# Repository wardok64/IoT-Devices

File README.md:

# Basic IoT devices to measure different field variables (based on Zigbee and MQTT)

This document details the final and functional design of a network of wireless sensors, established as End Devices and Coordinator within a Zigbee network, which, through its gateway consisting of the coordinator and an ESP12 communicated via UART data is sent to a MQTT Broker, and from there, it is possible to digitally display the data through NodeRED Dashboard.

The data sent from the end devices pertains to the value of the associated field sensor (it can be temperature, humidity or current), as well as the charge value of the battery that is powering it, in order to monitor the battery life and to protect the end device from low voltage.

## Initial requirements:

- Scalable software level via Zigbee and Node-RED.
- Battery powered field devices.
- Use MCU or development board with minimal elements to maximise power savings.
- Develop firmware with power saving option: "LowPower.h"/"RTCZero.h".
- Standard power supply for all field devices (3.3VDC).
- Scalability at hardware level.
- In the case of sensors with analogue signal, consider an ADC resolution between 12 and 16-bits.
- Low voltage protection in main power supply. (consider alarm via Zigbee).

## Sketch idea:

## Core materials HW:

- Seeeduino XIAO (ARM Cortex-M0+ CPU(SAMD21G18) running at up to 48MHz)
- Xbee XBP24 module Digi (XbeePROS2B).
- ESP8266/ESP-12 package.
- Raspberry Pi Zero W.

## Core Arduino libraries:

- Xbee.h
- PubSubClient.h
- RTCZero.h

## Software requirements:
  
- ArduinoIDE/VSC.
- XCTU (Digi).
- Node-RED/Dashboard.
- Mosquitto Broker.
- KiCAD.

## Sensors:

### Current:
- SCT-019-000 Current sensor/ Input current: 0-200A/ Output: 0-33mA (It needs burden resistor to convert to voltage).
- SCT-013-030 Current sensor/ Input current: 0-30A/ Output: 0-1Vrms. (incorporates its burden resistor)
- SCT-013-000 Current sensor/ Input current: 0-100A/ Output: 0-1Vrms. (incorporates its burden resistor)
  - Libraries:
    - emonlib.h (with some modifications.)

### Temperature:
- DS18B20.
  - Libraries:
    - OneWire.h
    - DallasTemperature.h
- RTD PT100 or PT1000 with MAX31865 Amplifer.
  - Libraries:
    - Adafruit_MAX31865.h
- Type K Thermocouple with MAX6675 controller.
  - Libraries:
    - max6675.h

### Relative Humidity and Temperature:
- SHT11.
  - Libraries:
    - SHT1x.h

## Summary:

The following is a basic project focused on the measurement, processing and monitoring of field variables in a semi-industrial process, in a rural area without direct access to internet or cellular networks, initially thought of solutions based on LoRa technology, SigFox or WiFi, but finally opted to use Zigbee using XbeePROS2B modules (apparently discontinued but currently low cost), The SAMD21G18 Cortex-M0 microcontroller, which is responsible for receiving and processing the signal from the field sensors and then send its value through Zigbee, was used Seeeduino-XIAO development board that incorporates the SAMD21 microcontroller for several reasons:
- [x] Compatible with Arduino IDE.
- [x] Multiple development interfaces and 11 digital/analog pins (ADC 10/12-bit).
- [x] Power Supply 3.3V/5V DC.
- [x] USB type-C Power supply and downloading interface.
- [x] Small size (20x17.5mm).
- [x] SWD Interface.
- [x] Easy project operation, Breadboard-friendly.

It was evaluated to use the development board Seeeduino XIAO, this development board unlike an Arduino nano, does not have an FTDI chip, as this is programmed directly with a USB chip, which allows us to save energy while the device is not being programmed, ie the FTDI circuit in the Arduino nano, is draining current, even if it is not being used at that time, another alternative was to use the Arduino mini, but it is officially discontinued and is only available in clone.

We should also mention that this development board has a 3.3V linear output voltage regulator, the XC6206 which allows us to perfectly power our Xbee.

## Hardware modifications:

Along with the use of the RTC library that fits perfectly to put the MCU in power saving mode, here is a table with current consumptions considering the user LED (PA17) embedded on the board, as well as the power LED:

| Conditions    | Results       | Details       |
| ------------- | ------------- | ------------- |
| Input voltage via USB-C port: 4.95V, LED flashes every second | 12,4 mA a 4,95 V (61,38 mW)  | Measured when the flashing LED is on. |
| Input voltage via USB-C port: 4.95V, Sleep mode with RTCZero library| 2,2 mA a 4,95 V (10,89 mW)|The MCU itself uses less than 1mA (the RTC and some other services are active), the rest is used by the power LED and the voltage regulator.|

In our case, we chose to eliminate the power LED, which consumes current all the time, when the XIAO is powered (Corresponds to GREEN PWR), this was extracted from the diagram:

Among the examples of the RTC library, there is a basic one, which places the microcontroller in sleep mode for a programmed time, when the time is over, it wakes up and turns on its LED. The example can be found as: "sleepRTCAlarm.ino" Once we verify that the library works correctly, we load it to our Seeeduino XIAO board, then we measure the current consumption in sleep mode, with a multimeter, giving us as a result of the readings the following values:

| Seeeduino-XIAO ||||
| ------------- | ------------- | ------------- | ------------- |
|Normal mode with power LED on.|Sleep Mode with activated power LED.|Normal mode without power LED.|Sleep Mode without power LED.|
|14.40mA|1.40mA|12.60mA|0.08mA|

> [!NOTE]
> Power LED, as for example on the Arduino UNO board, this LED indicates when the board is powered.

## Configuracion Sleep-Mode en XCTU:

The parameters for our XbeePROS2B to go into sleep mode, but through external control, i.e. to put the Xbee to sleep and wake it up by commands from the SAMD21. The sleep settings are as follows in XCTU:

## Code descriptions:

We define a macro for pin D10 (11) pin to manipulate Xbee Sleep-Mode.
```
#define SleepXbee 10 
```
We define a macro for pin D9 (10) pin to identify when our xbee has connected to the zigbee network.
```
#define AssLEDEN   9 
```
This pin corresponds to an association signal from our Xbee, which is indicated in the data sheet:

> ### Associate LED:
> The Associate pin (pin 15) provides an indication of the device's sleep status and diagnostic information. To take advantage of these indications, connect an LED to the Associate pin. To enable the Associate LED functionality, set the D5 command to 1; it is enabled by default. If enabled, the Associate pin is configured as an output. This section describes the behavior of the pin. The Associate pin indicates the synchronization status of a sleep compatible XBee/XBee-PRO DigiMesh 2.4. If a device is not sleep compatible, the pin functions as a power indicator. Use the LT command to override the blink rate of the Associate pin. If you set LT to 0, the device uses the default blink time: 500 ms for a sleep coordinator, 250 ms otherwise. The following table describes the Associate LED functionality.

Source: [DIGI Documentation](https://www.digi.com/resources/documentation/Digidocs/90000991/reference/r_associate_led.htm?TocPath=Work%20with%20networked%20devices%7CTest%20links%20between%20adjacent%20devices%7C_____6)

## Basic connection diagram between Xbee and Seeeduino-XIAO:

## Power consumption:

Table of total current consumption Xbee+Seeduino XIAO.
| XIAO SAMD21 + XBee Pro S2B Current with same power supply |-|
| ------------- | ------------- |
|Sleep-Mode Xbee + XIAO|Transmision Mode Zigbee|
|0.09mA.|30-60mA.|

> [!NOTE]
> The maximum average time from the time the End Device wakes up, establishes a connection with the network coordinator, and sends the data frame is 15 seconds.

> [!NOTE]
> It was determined that the best way for our MCU to verify when our Xbee has been associated to a Zigbee network is to use the Assossiate LED pin, which by means of a counter, indicates when the Xbee has successfully connected to the network and is ready to send a data, this pin is digital, so it can work perfectly as an input for the XIAO Seeeduino.

## Prototyping for proof of concept:

### End devices.

### Coordinador conected to XCTU.

Variable value:

Battery value:

### Coordinador with Arduino UNO.

By running the serial monitor of our Arduino UNO we can observe the composition of our frame, both Zigbee reception and MQTT sending.

## Gateway Zigbee To MQTT:

### Prototyping (Proof of concept).

As mentioned before, the main function of our gateway is to establish a MQTT connection with the Broker server via WIFI (maybe in the future an Ethernet connection will be considered, to guarantee stability), receive the data from the end devices, with the help of our library "xbee. h" library, it identifies the ID of the end device that sent the message, then it processes the message and it starts to send a structured string of characters, which will correspond to the specific topic of the device, finally it publishes the topic and the corresponding payload (a status LED was added to indicate each of the operations).

Diagram:

For the electronic design we considered, among other things, a selector and connectors that allow us on the one hand to reconfigure the operating parameters of our Xbee, and on the other hand a firmware update of the MCU ESP8266 (via SERIAL).

Code:
Local IP/DNS of Broker MQTT (RaspberryPi).
```
const char* mqtt_server = "nodered.local"; 
```
Connect with Broker MQTT, port 1883 (local/insecure).
```
client.setServer(mqtt_server, 1883);
```
Get payload from Zigbee.
```
for (int i = 9; i < rx.getDataLength(); i++) 
    {
      payload += (char)rx.getData(i);
    }
```
Get remote address, store in strings.
```
SH = String(rx.getRemoteAddress64().getMsb(),HEX);
SL = String(rx.getRemoteAddress64().getLsb(),HEX);
```

Define MQTT topic.
```
String topic = "/line/area/equipment/";
```
Concatenate new topic.
```
topic_ = topic + elemento + slash + variable + slash + SL;
```
Convert String to Char array.
```
char _SL[39];
topic_.toCharArray(_SL,39);
```
Publish to MQTT.
```
client.publish(_SL, _payload);
```

## Node-RED

If we power our Gateway, and connect our nodes, we must first energize and connect our Raspberry pi to the common modem, to run, first the MQTT broker, then a NodeRED client that runs inside the same Raspberry Pi, now through our PC, we can access NodeRED and also open our MQTT.fx application to view the topics and payload that are being sent to the Broker, as shown in the following images:

MQTT.fx

Node-RED.

Initially the MQTTin nodes subscribed to each of the corresponding topicals for each end device were individually configured, the corresponding payload was filtered from the value of the field variable and the battery charge value of each device.

Node-RED/Dashboard.

A fairly basic dashboard design was developed to display the values (Front-End).

## KICAD and PCB.

End devices.

Once some proofs of concept, testing, debugging and dimensioning adjustments were done, we proceeded to the design in KiCAD of the final devices, keeping in mind the modularity so that each of the final devices is compatible with different types of sensors.

The electronic design was done in KiCAD working with two layers.

The manufacturing of the circuits was sent to China.

Gateway.

## Final Architecture:

As a conclusion in the development of this project I can mention that the devices are working functionally in a semi-industrial environment, each element of the network was protected with an enclosure of suitable grade (IP67). Any part of the project (software and hardware) is 100% improvable, to mention a few; 

- Use of ethernet instead of WiFi.
- Migration to DIGI mesh.
- Migration to ESP32.
- Bare-metal firmware programming to avoid library dependencies as much as possible (optimizing energy consumption).
- Among others.

## Next steps:
- [ ] Migrate XbeePROS2B to S3B or DigiMesh.
- [ ] Low-Cost Field Network version with ESP-NOW.
- [ ] Gateway ESP-NOW to MQTT with ESP32.
- [ ] Dashboard remote from internet.
- [ ] Enable Low-Power.
- [ ] Interchangeable modular sensors.
- [ ] Add more field sensors.
- [ ] Add more connectors.

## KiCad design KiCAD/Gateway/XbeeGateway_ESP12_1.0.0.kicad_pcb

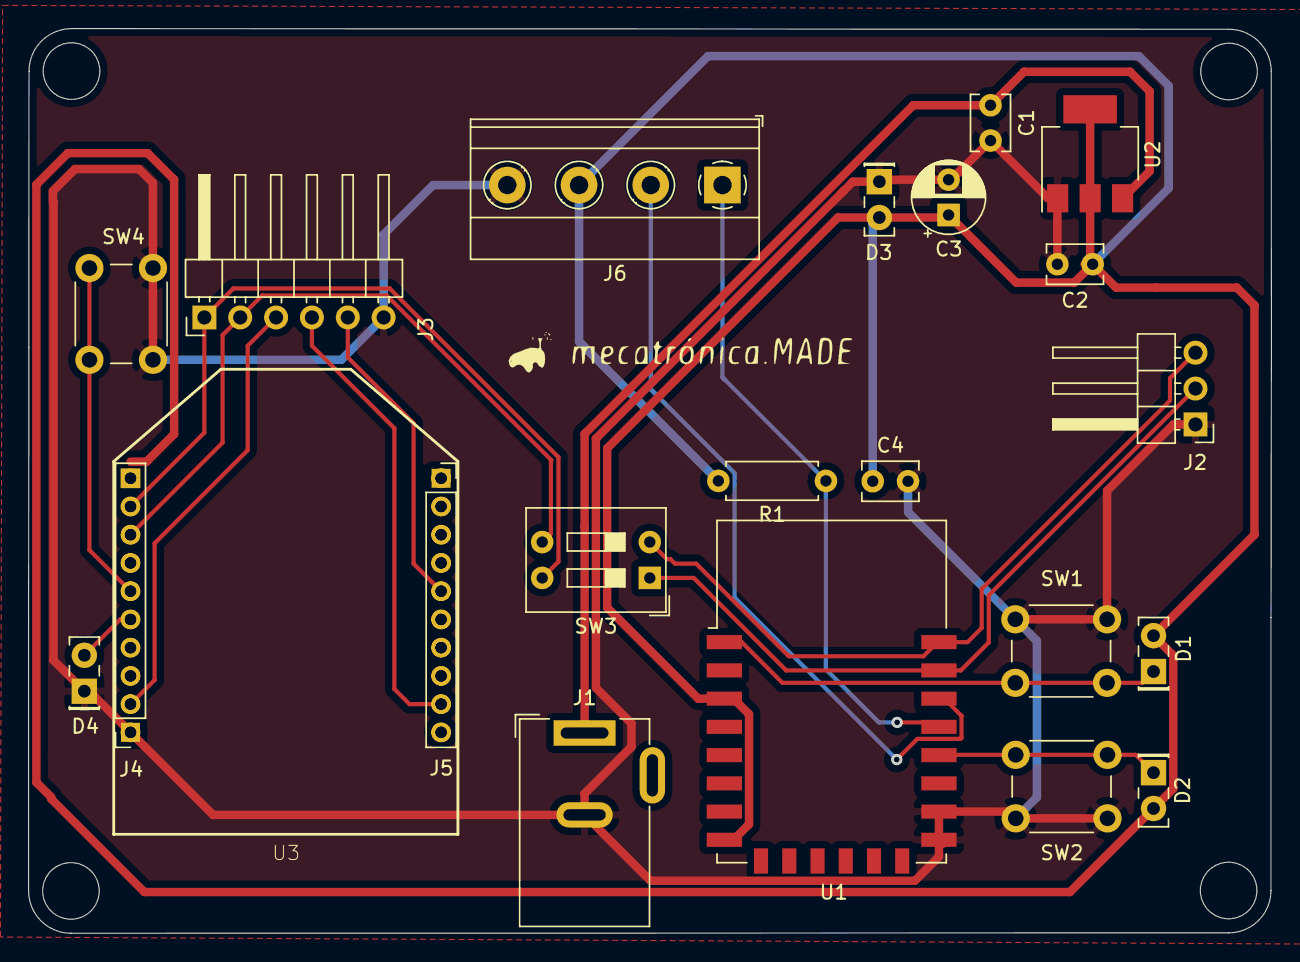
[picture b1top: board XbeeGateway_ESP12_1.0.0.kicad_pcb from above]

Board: 2 copper layers, 88.0 x 64.1 mm, 22 parts (0 on the bottom side), 16 nets.

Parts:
C1, C2: C; C_Disc_D3.8mm_W2.6mm_P2.50mm
C3: CP; CP_Radial_D5.0mm_P2.50mm
C4: 100nF; C_Disc_D3.8mm_W2.6mm_P2.50mm
D1, D2, D3, D4: LED; LED_Rectangular_W5.0mm_H2.0mm
J1: Jack-DC; BarrelJack_Wuerth_6941xx301002
J2: Conn_01x03_Male; PinHeader_1x03_P2.54mm_Horizontal
J3: Conn_01x06_Male; PinHeader_1x06_P2.54mm_Horizontal
J4, J5: Conn_01x10_Female; PinSocket_1x10_P2.00mm_Vertical
J6: Conn_01x04_Male; TerminalBlock_Phoenix_MKDS-1,5-4-5.08_1x04_P5.08mm_Horizont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
R1: 10K; R_Axial_DIN0207_L6.3mm_D2.5mm_P7.62mm_Horizontal
SW1, SW2, SW4: SW_Push; SW_PUSH_6mm
SW3: SW_DIP_x02; SW_DIP_SPSTx02_Slide_9.78x7.26mm_W7.62mm_P2.54mm
U1: ESP-12E
U2: AMS1117-3.3; SOT-223-3_TabPin2
U3: XBP9B-DMST-002; DIP2200W51P200L3294H279Q20P

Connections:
+3V3: C2.1, C3.1, C4.1, D1.2, D2.2, D3.2, J6.3, R1.2, U1.3, U1.8, U2.2, U3.1
+12V: C1.1, J1.1, U2.3
/CTS: J3.4, J5.9, U3.12
/DIN: J3.2, J4.8, SW3.3, U3.3
/DOUT: J3.1, J4.9, SW3.4, U3.2
/DTR: J3.3, J4.2, U3.9
/RTS: J3.5, J5.5, U3.16
DATA: J6.1, R1.1, U1.19
GND: C1.2, C2.2, C3.2, C4.2, D3.1, D4.1, J1.2, J2.1, J3.6, J4.1, J6.4, SW1.1, SW2.2, SW4.1, U1.15, U1.16, U2.1, U3.10
unnamed: D1.1, SW1.2, U1.1
unnamed: D2.1, SW2.1, U1.18
RESET: J4.6, SW4.2, U3.5
RSSI: D4.2, J4.5, U3.6
Rx: J2.2, SW3.1, U1.21
SCK: J6.2, U1.20
Tx: J2.3, SW3.2, U1.22

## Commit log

2024-01-05 Create main.c
    Code for basic Zigbee to MQTT gateway
